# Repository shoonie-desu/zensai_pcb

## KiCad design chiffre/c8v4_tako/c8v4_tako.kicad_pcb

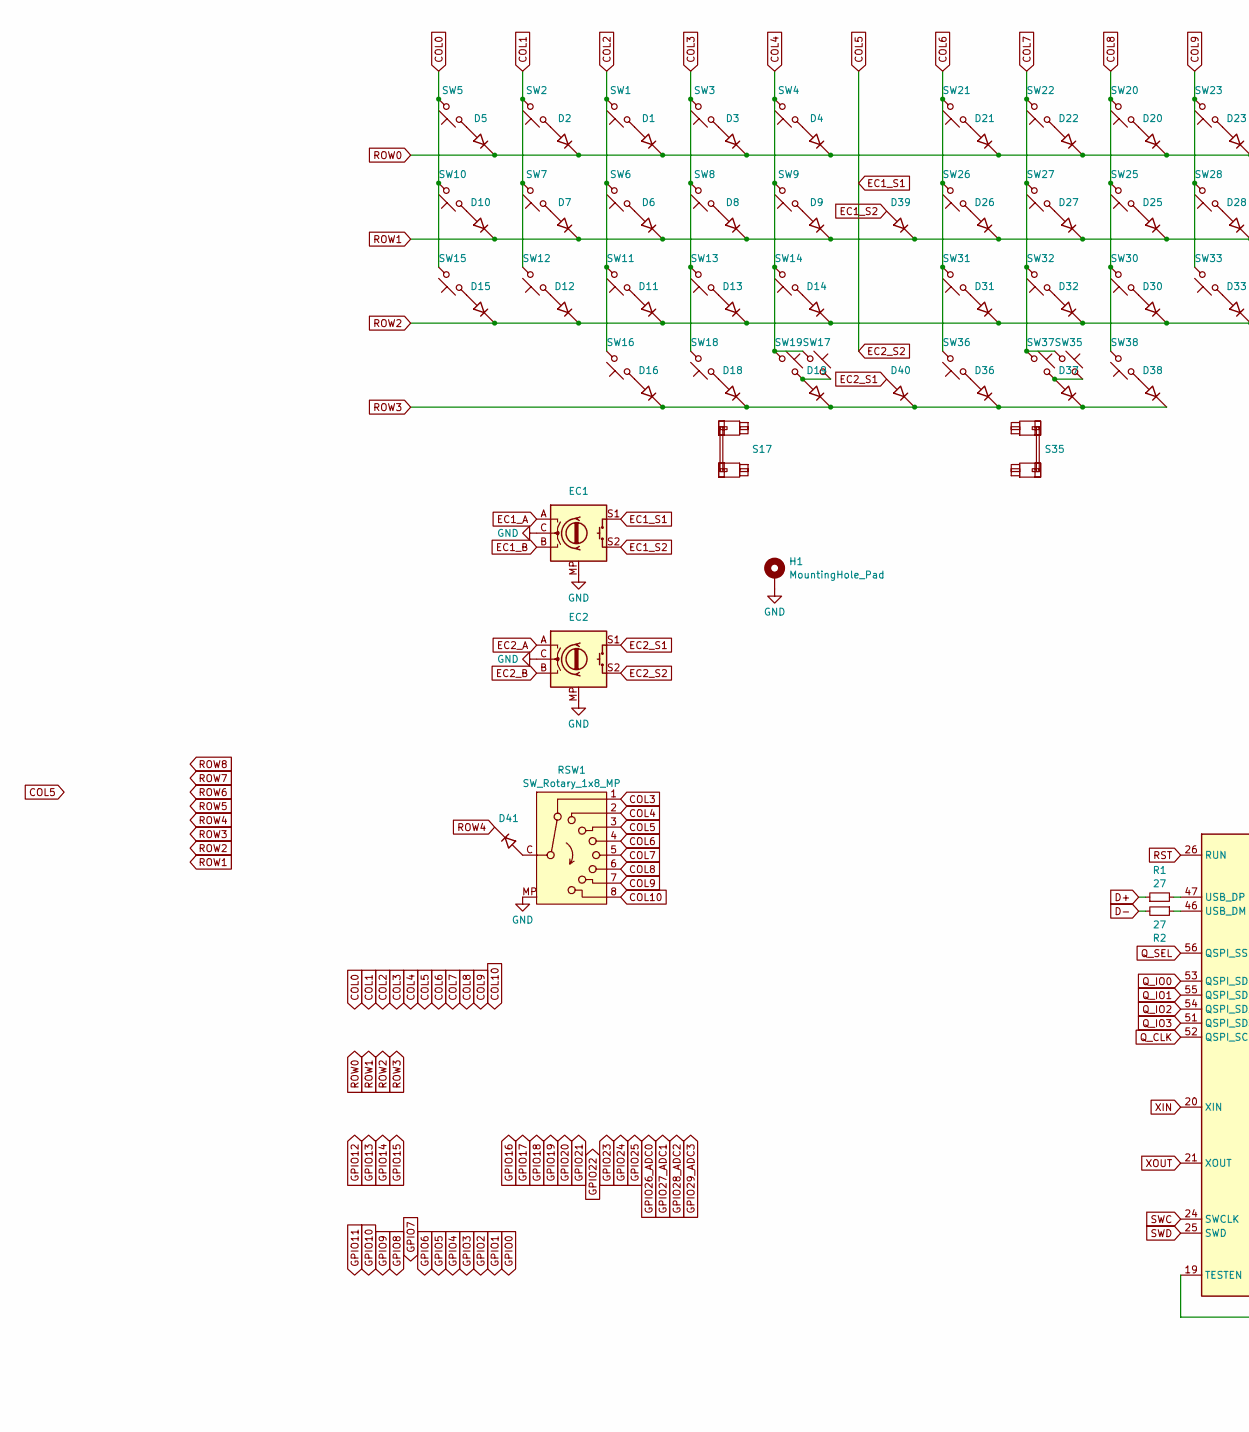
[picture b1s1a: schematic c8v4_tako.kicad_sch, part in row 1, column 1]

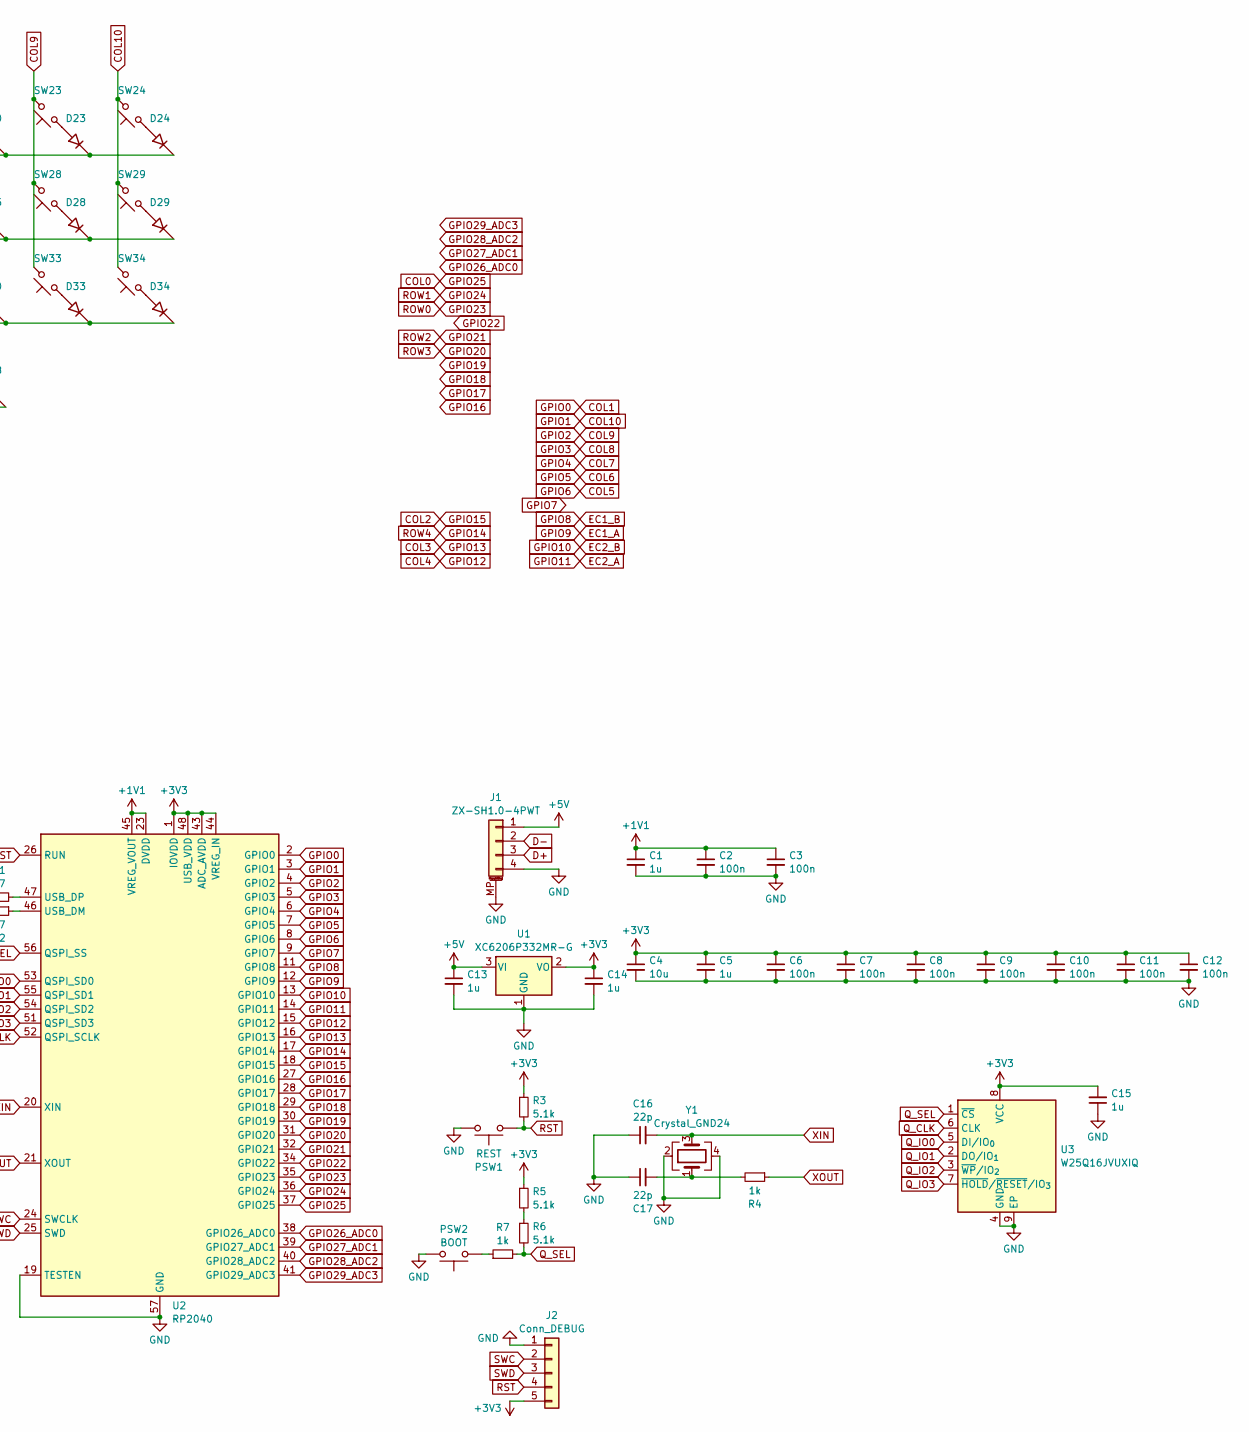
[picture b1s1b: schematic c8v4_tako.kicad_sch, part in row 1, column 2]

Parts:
C1, C5, C13, C14, C15: 1u; C_0402_1005Metric_mod
C2, C3, C6, C7, C8, C9, C10, C11, C12: 100n; C_0402_1005Metric_mod
C4: 10u; C_0402_1005Metric_mod
C16, C17: 22p; C_0402_1005Metric_mod
D1, D2, D3, D4, D5, D6, D7, D8, D9, D10, D11, D12, D13, D14, D15, D16, D18, D19, D20, D21, D22, D23, D24, D25, D26, D27, D28, D29, D30, D31, D32, D33, D34, D36, D37, D38, D39, D40, D41: 1N4148W; D_SOD-123_mod
EC1, EC2: RotaryEncoder_Switch_MP; ROT_Alps_EC11E-Switch_mod
H1: MountingHole_Pad; MountingHole_3.2mm_M3_Pad_TopBottom
J1: ZX-SH1.0-4PWT; JST_SH_SM04B-SRSS-TB_1x04-1MP_P1.00mm_Horizontal
J2: Conn_DEBUG; PinHeader_1x05_P1.27mm_Vertical
PSW1: REST; JUMP_REST_10.16mm
PSW2: BOOT; JUMP_BOOT_10.16mm
R1, R2: 27; R_0402_1005Metric
R3, R5, R6: 5.1k; R_0402_1005Metric
R4, R7: 1k; R_0402_1005Metric
RSW1: SW_Rotary_1x8_MP; alpsalpine_SRBV
S17, S35: MX_S; STAB_MX_2u
SW1, SW2, SW3, SW4, SW5, SW6, SW7, SW8, SW9, SW10, SW11, SW12, SW13, SW14, SW15, SW16, SW17, SW18, SW19, SW20, SW21, SW22, SW23, SW24, SW25, SW26, SW27, SW28, SW29, SW30, SW31, SW32, SW33, SW34, SW35, SW36, SW37, SW38: CPG151101S11; SW_MX_HS_S_CPG151101S11_1u_mod; LCSC Part # C49352235
U1: XC6206P332MR-G; SOT-23-3
U2: RP2040; QFN-56-1EP_7x7mm_P0.4mm_EP3.2x3.2mm; LCSC Part # C2040
U3: W25Q16JVUXIQ; Winbond_USON-8-1EP_3x2mm_P0.5mm_EP0.2x1.6mm
Y1: Crystal_GND24; Crystal_SMD_3225-4Pin_3.2x2.5mm; LCSC Part # C403945

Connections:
+1V1: C1.1, C2.1, C3.1, U2.23 (DVDD), U2.45 (VREG_VOUT), U2.50 (DVDD)
+3V3: C4.1, C5.1, C6.1, C7.1, C8.1, C9.1, C10.1, C11.1, C12.1, C14.1, C15.2, J2.5, R3.1, R5.1, U1.2 (VO), U2.1 (IOVDD), U2.10 (IOVDD), U2.22 (IOVDD), U2.33 (IOVDD), U2.42 (IOVDD), U2.43 (ADC_AVDD), U2.44 (VREG_IN), U2.48 (USB_VDD), U2.49 (IOVDD), U3.8 (VCC)
+5V: C13.1, J1.1, U1.3 (VI)
COL0: SW5.2, SW10.2, SW15.2, U2.37 (GPIO25)
COL1: SW2.2, SW7.2, SW12.2, U2.2 (GPIO0)
COL2: SW1.2, SW6.2, SW11.2, SW16.2, U2.18 (GPIO15)
COL3: RSW1.1, SW3.2, SW8.2, SW13.2, SW18.2, U2.16 (GPIO13)
COL4: RSW1.2, SW4.2, SW9.2, SW14.2, SW17.1, SW19.1, U2.15 (GPIO12)
COL5: EC1.S1, EC2.S2, RSW1.3, U2.8 (GPIO6)
COL6: RSW1.4, SW21.2, SW26.2, SW31.2, SW36.2, U2.7 (GPIO5)
COL7: RSW1.5, SW22.2, SW27.2, SW32.2, SW35.1, SW37.1, U2.6 (GPIO4)
COL8: RSW1.6, SW20.2, SW25.2, SW30.2, SW38.2, U2.5 (GPIO3)
COL9: RSW1.7, SW23.2, SW28.2, SW33.2, U2.4 (GPIO2)
COL10: RSW1.8, SW24.2, SW29.2, SW34.2, U2.3 (GPIO1)
D+: J1.3, R1.1
D-: J1.2, R2.2
EC1_A: EC1.A, U2.12 (GPIO9)
EC1_B: EC1.B, U2.11 (GPIO8)
EC1_S2: D39.2 (A), EC1.S2
EC2_A: EC2.A, U2.14 (GPIO11)
EC2_B: EC2.B, U2.13 (GPIO10)
EC2_S1: D40.2 (A), EC2.S1
GND: C1.2, C2.2, C3.2, C4.2, C5.2, C6.2, C7.2, C8.2, C9.2, C10.2, C11.2, C12.2, C13.2, C14.2, C15.1, C16.1, C17.1, EC1.C, EC1.MP, EC2.C, EC2.MP, H1.1, J1.4, J1.MP (MountPin), J2.1, PSW1.1, PSW2.1, RSW1.MP, U1.1 (GND), U2.19 (TESTEN), U2.57 (GND), U3.4 (GND), U3.9 (EP), Y1.2, Y1.4; also elsewhere on the board
GPIO7: U2.9 (GPIO7)
GPIO14: D41.1 (K), U2.17 (GPIO14)
GPIO16: U2.27 (GPIO16)
GPIO17: U2.28 (GPIO17)
GPIO18: U2.29 (GPIO18)
GPIO19: U2.30 (GPIO19)
GPIO20: D16.1 (K), D18.1 (K), D19.1 (K), D36.1 (K), D37.1 (K), D38.1 (K), D40.1 (K), U2.31 (GPIO20)
GPIO21: D11.1 (K), D12.1 (K), D13.1 (K), D14.1 (K), D15.1 (K), D30.1 (K), D31.1 (K), D32.1 (K), D33.1 (K), D34.1 (K), U2.32 (GPIO21)
GPIO22: U2.34 (GPIO22)
GPIO23: D1.1 (K), D2.1 (K), D3.1 (K), D4.1 (K), D5.1 (K), D20.1 (K), D21.1 (K), D22.1 (K), D23.1 (K), D24.1 (K), U2.35 (GPIO23)
GPIO24: D6.1 (K), D7.1 (K), D8.1 (K), D9.1 (K), D10.1 (K), D25.1 (K), D26.1 (K), D27.1 (K), D28.1 (K), D29.1 (K), D39.1 (K), U2.36 (GPIO24)
GPIO26_ADC0: U2.38 (GPIO26_ADC0)
GPIO27_ADC1: U2.39 (GPIO27_ADC1)
GPIO28_ADC2: U2.40 (GPIO28_ADC2)
GPIO29_ADC3: U2.41 (GPIO29_ADC3)
unnamed: C17.2, R4.2, Y1.1
unnamed: D1.2 (A), SW1.1
unnamed: D2.2 (A), SW2.1
unnamed: D3.2 (A), SW3.1
unnamed: D4.2 (A), SW4.1
unnamed: D5.2 (A), SW5.1
unnamed: D6.2 (A), SW6.1
unnamed: D7.2 (A), SW7.1
unnamed: D8.2 (A), SW8.1
unnamed: D9.2 (A), SW9.1
unnamed: D10.2 (A), SW10.1
unnamed: D11.2 (A), SW11.1
unnamed: D12.2 (A), SW12.1
unnamed: D13.2 (A), SW13.1
unnamed: D14.2 (A), SW14.1
unnamed: D15.2 (A), SW15.1
unnamed: D16.2 (A), SW16.1
unnamed: D18.2 (A), SW18.1
unnamed: D19.2 (A), SW17.2, SW19.2
unnamed: D20.2 (A), SW20.1
unnamed: D21.2 (A), SW21.1
unnamed: D22.2 (A), SW22.1
unnamed: D23.2 (A), SW23.1
unnamed: D24.2 (A), SW24.1
unnamed: D25.2 (A), SW25.1
unnamed: D26.2 (A), SW26.1
unnamed: D27.2 (A), SW27.1
unnamed: D28.2 (A), SW28.1
unnamed: D29.2 (A), SW29.1
unnamed: D30.2 (A), SW30.1
unnamed: D31.2 (A), SW31.1
unnamed: D32.2 (A), SW32.1
unnamed: D33.2 (A), SW33.1
unnamed: D34.2 (A), SW34.1
unnamed: D36.2 (A), SW36.1
unnamed: D37.2 (A), SW35.2, SW37.2
unnamed: D38.2 (A), SW38.1
unnamed: D41.2 (A), RSW1.C
unnamed: PSW2.2, R7.1
unnamed: R5.2, R6.1
unnamed: R2.1, U2.46 (USB_DM)
unnamed: R1.2, U2.47 (USB_DP)
Q_CLK: U2.52 (QSPI_SCLK), U3.6 (CLK)
Q_IO0: U2.53 (QSPI_SD0), U3.5 (DI/IO_{0})
Q_IO1: U2.55 (QSPI_SD1), U3.2 (DO/IO_{1})
Q_IO2: U2.54 (QSPI_SD2), U3.3 (~WP/IO_{2})
Q_IO3: U2.51 (QSPI_SD3), U3.7 (~HOLD/~RESET/IO_{3})
Q_SEL: R6.2, R7.2, U2.56 (QSPI_SS), U3.1 (~CS)
RST: J2.4, PSW1.2, R3.2, U2.26 (RUN)
SWC: J2.2, U2.24 (SWCLK)
SWD: J2.3, U2.25 (SWD)
XIN: C16.2, U2.20 (XIN), Y1.3
XOUT: R4.1, U2.21 (XOUT)

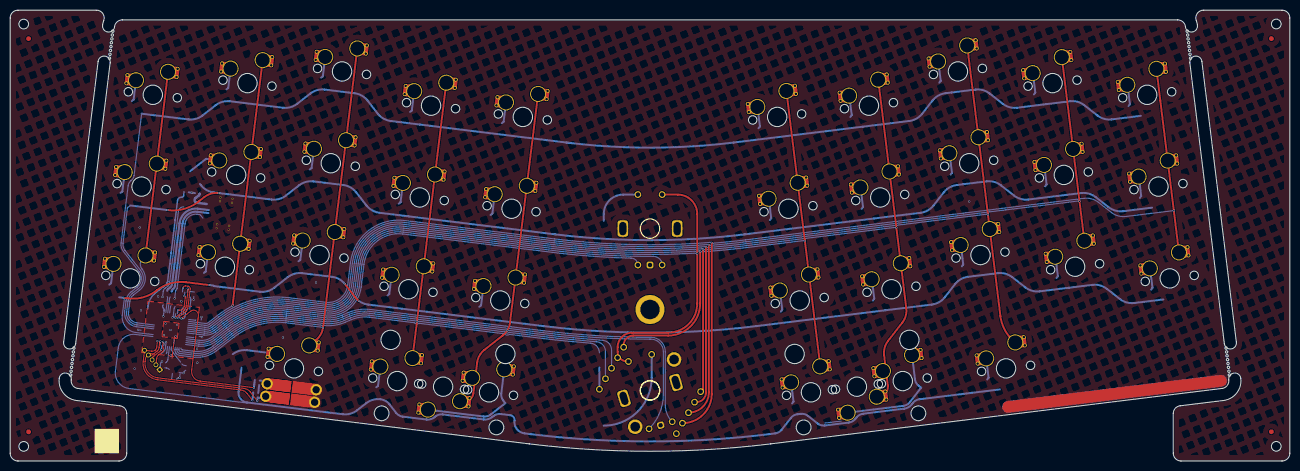
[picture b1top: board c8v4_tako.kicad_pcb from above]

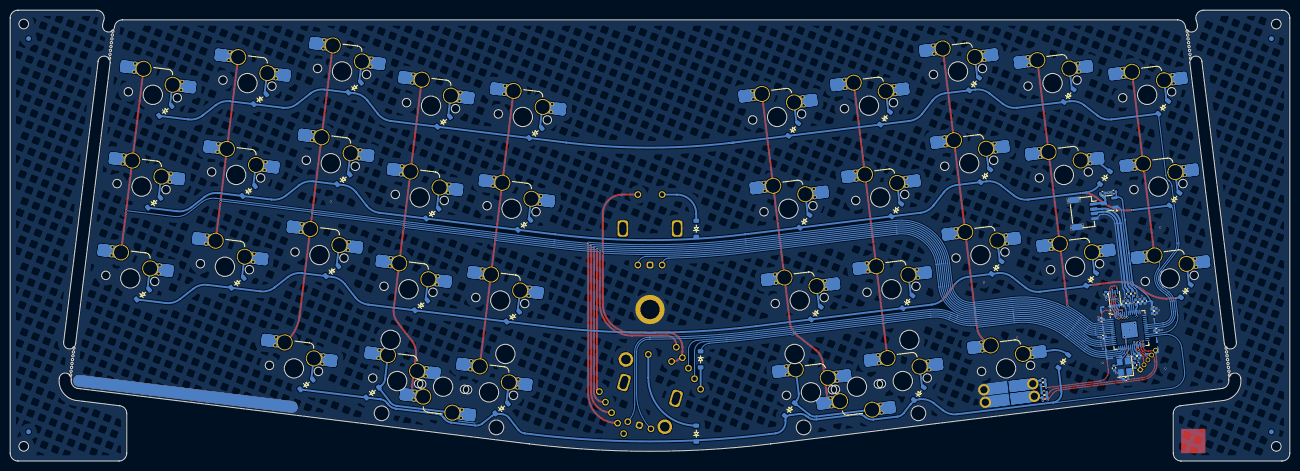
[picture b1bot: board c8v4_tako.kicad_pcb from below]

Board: 2 copper layers, 263.6 x 92.8 mm, 119 parts (112 on the bottom side), 81 nets.

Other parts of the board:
H1#2, H1#3, H1#4, H1#5: MountingHole_Pad; MountingHole_3.2mm_M3_Pad_TopBottom

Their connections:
GND: H1#2.1; also elsewhere on the board

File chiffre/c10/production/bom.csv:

Designator,Footprint,Quantity,Value,LCSC Part #
"C1, C13, C14, C15, C5",0402,5,1u,
"C10, C11, C12, C2, C3, C6, C7, C8, C9",0402,9,100n,
"C16, C17",0402,2,22p,
C4,0402,1,10u,
"D1, D10, D11, D12, D13, D14, D15, D16, D18, D19, D2, D20, D21, D22, D23, D24, D25, D26, D27, D28, D29, D3, D30, D31, D32, D33, D34, D36, D37, D38, D39, D4, D40, D41, D5, D6, D7, D8, D9",D_SOD-123_mod,39,1N4148W,
J1,JST_SH_SM04B-SRSS-TB_1x04-1MP_P1.00mm_Horizontal,1,ZX-SH1.0-4PWT,
"R1, R2",0402,2,27,
"R3, R5, R6",0402,3,5.1k,
"R4, R7",0402,2,1k,
RSW1,alpsalpine_SRBV,1,SW_Rotary_1x8_MP,
"SW1, SW10, SW11, SW12, SW13, SW14, SW15, SW16, SW17, SW18, SW19, SW2, SW20, SW21, SW22, SW23, SW24, SW25, SW26, SW27, SW28, SW29, SW3, SW30, SW31, SW32, SW33, SW34, SW35, SW36, SW37, SW38, SW4, SW5, SW6, SW7, SW8, SW9",SW_MX_HS_S_CPG151101S11_1u_mod,38,CPG151101S11,
U1,SOT-23-3,1,XC6206P332MR-G,
U2,QFN-56-1EP_7x7mm_P0.4mm_EP3.2x3.2mm,1,RP2040,
U3,Winbond_USON-8-1EP_3x2mm_P0.5mm_EP0.2x1.6mm,1,W25Q16JVUXIQ,
Y1,Crystal_SMD_3225-4Pin_3.2x2.5mm,1,Crystal_GND24,

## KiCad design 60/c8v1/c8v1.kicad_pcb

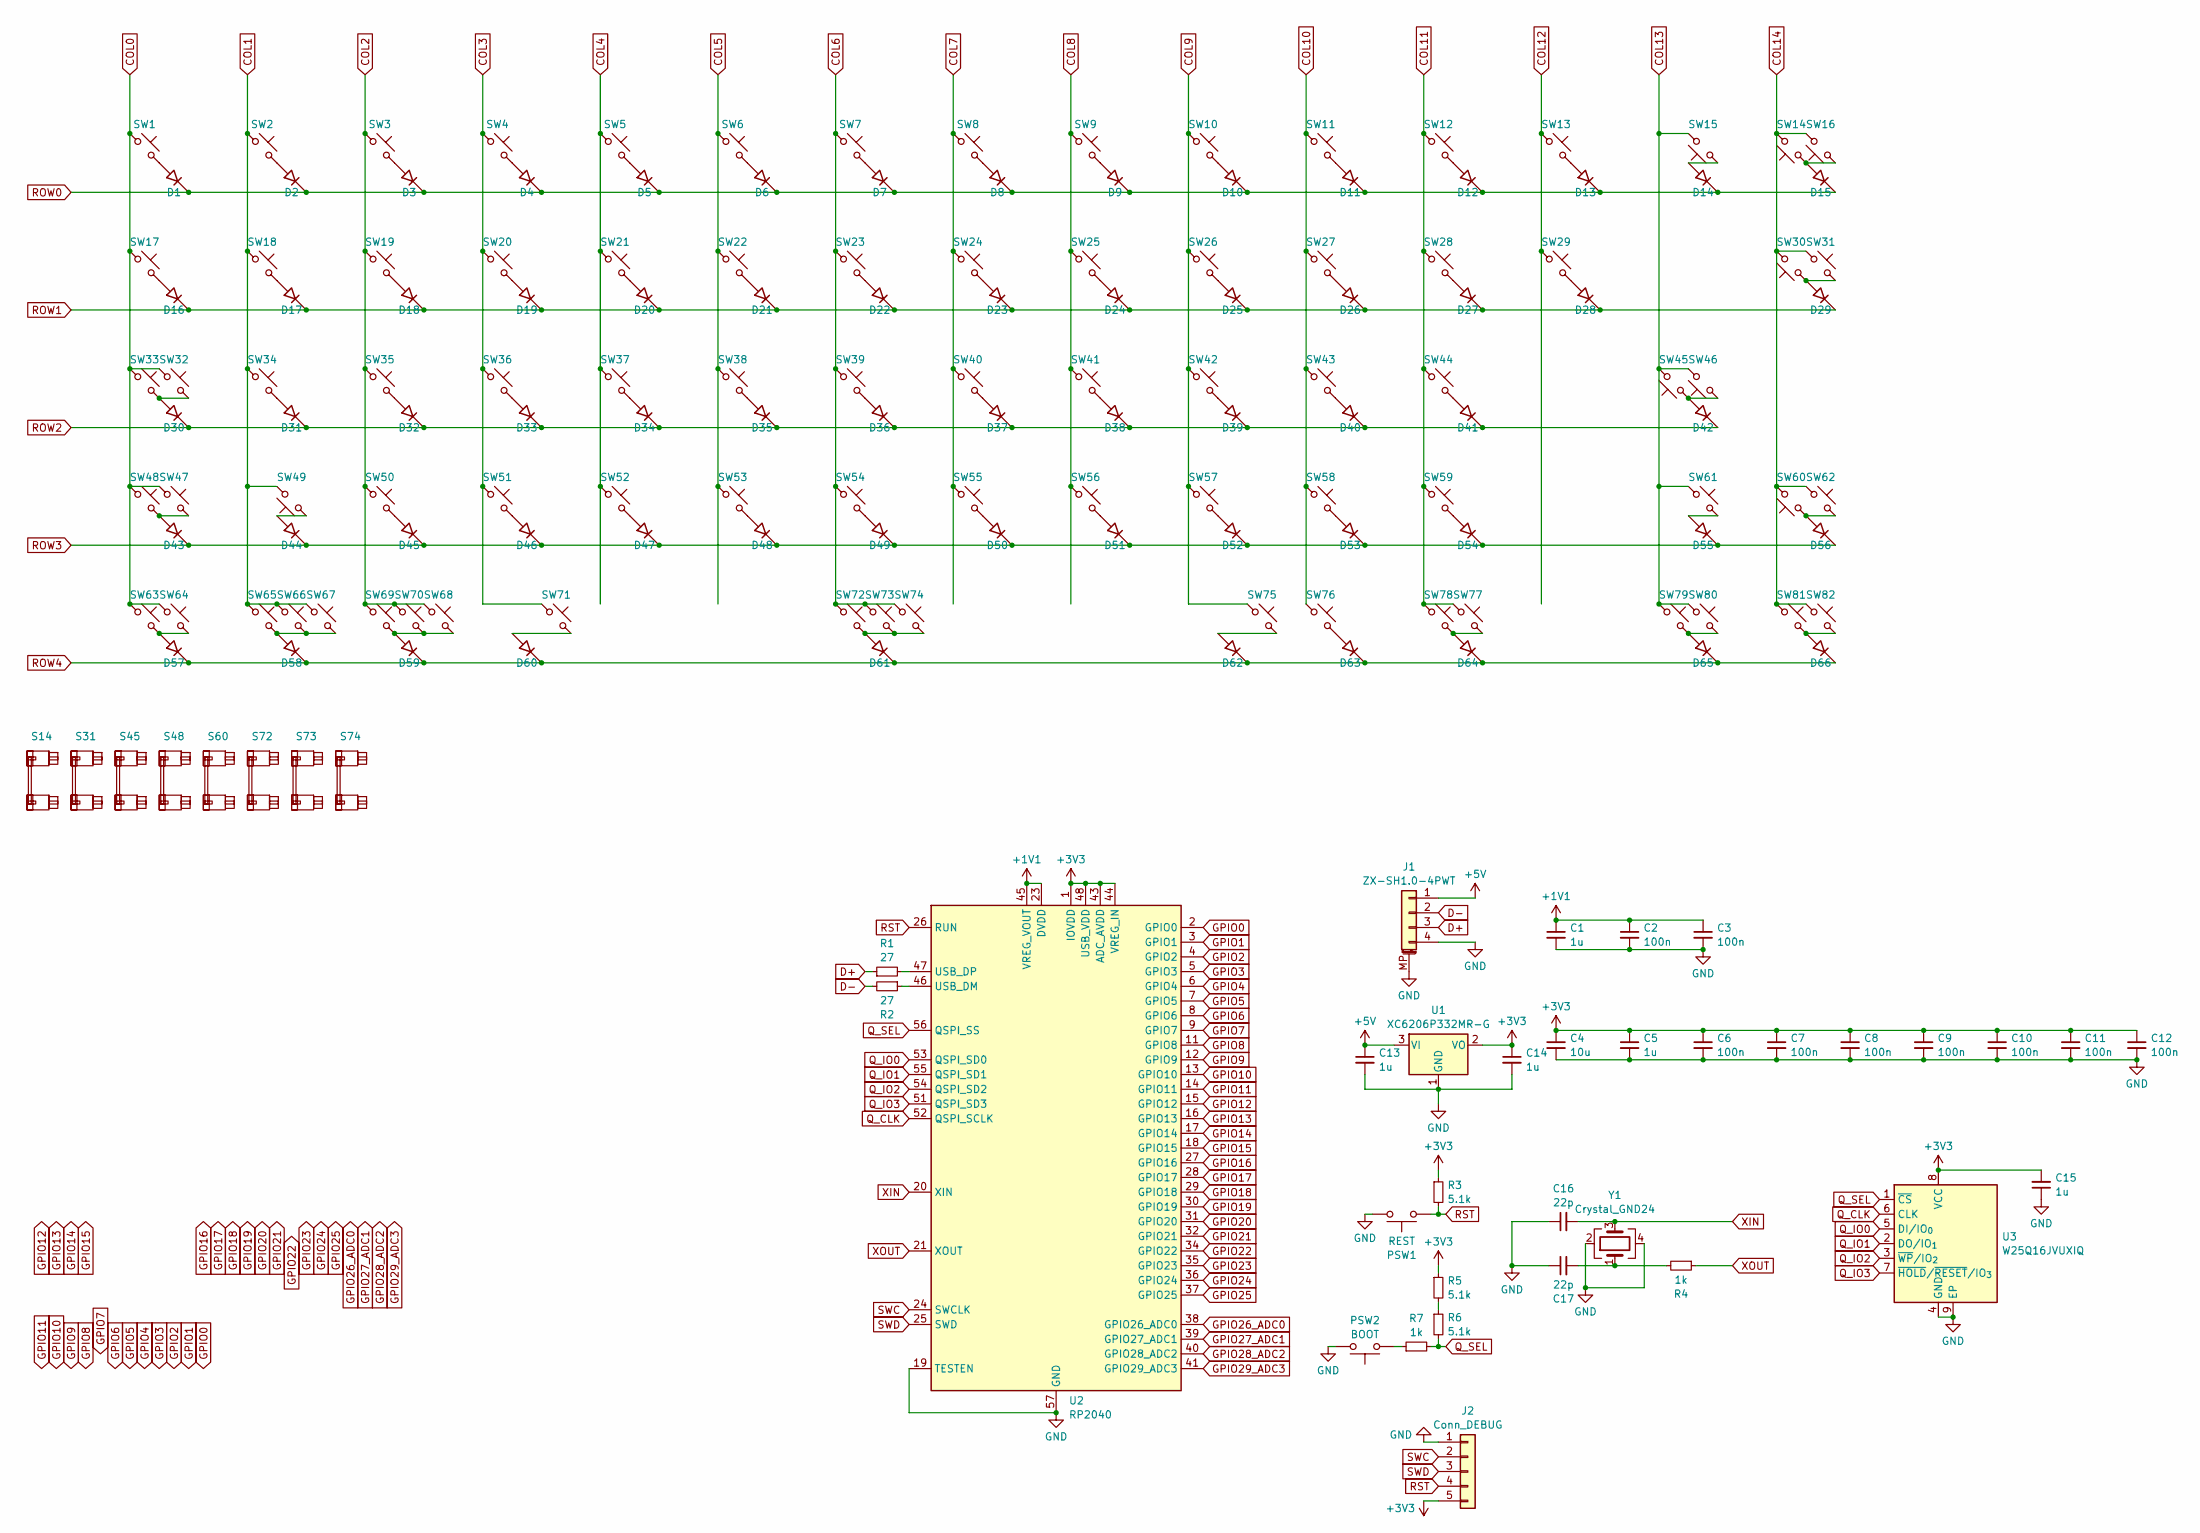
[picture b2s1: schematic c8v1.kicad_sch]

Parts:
C1, C5, C13, C14, C15: 1u; C_0402_1005Metric_mod
C2, C3, C6, C7, C8, C9, C10, C11, C12: 100n; C_0402_1005Metric_mod
C4: 10u; C_0402_1005Metric_mod
C16, C17: 22p; C_0402_1005Metric_mod
D1, D2, D3, D4, D5, D6, D7, D8, D9, D10, D11, D12, D13, D14, D15, D16, D17, D18, D19, D20, D21, D22, D23, D24, D25, D26, D27, D28, D29, D30, D31, D32, D33, D34, D35, D36, D37, D38, D39, D40, D41, D42, D43, D44, D45, D46, D47, D48, D49, D50, D51, D52, D53, D54, D55, D56, D57, D58, D59, D60, D61, D62, D63, D64, D65, D66: 1N4148W; D_SOD-123_mod
J1: ZX-SH1.0-4PWT; JST_SH_SM04B-SRSS-TB_1x04-1MP_P1.00mm_Horizontal
J2: Conn_DEBUG; PinHeader_1x05_P1.27mm_Vertical
PSW1: REST; JUMP_REST_10.16mm
PSW2: BOOT; JUMP_BOOT_10.16mm
R1, R2: 27; R_0402_1005Metric
R3, R5, R6: 5.1k; R_0402_1005Metric
R4, R7: 1k; R_0402_1005Metric
S14, S31, S45, S48, S60: MX_S; STAB_MX_2u
S72: MX_S; STAB_MX_4.5u
S73: MX_S; STAB_MX_6.25u
S74: MX_S; STAB_MX_7u
SW1, SW2, SW3, SW4, SW5, SW6, SW7, SW8, SW9, SW10, SW11, SW12, SW13, SW14, SW15, SW16, SW17, SW18, SW19, SW20, SW21, SW22, SW23, SW24, SW25, SW26, SW27, SW28, SW29, SW30, SW31, SW32, SW33, SW34, SW35, SW36, SW37, SW38, SW39, SW40, SW41, SW42, SW43, SW44, SW45, SW46, SW47, SW48, SW49, SW50, SW51, SW52, SW53, SW54, SW55, SW56, SW57, SW58, SW59, SW60, SW61, SW62, SW63, SW64, SW65, SW66, SW67, SW68, SW69, SW70, SW71, SW72, SW73, SW74, SW75, SW76, SW77, SW78, SW79, SW80, SW81, SW82: CPG151101S11; SW_MX_1u_mod
U1: XC6206P332MR-G; SOT-23-3
U2: RP2040; QFN-56-1EP_7x7mm_P0.4mm_EP3.2x3.2mm
U3: W25Q16JVUXIQ; Winbond_USON-8-1EP_3x2mm_P0.5mm_EP0.2x1.6mm
Y1: Crystal_GND24; Crystal_SMD_3225-4Pin_3.2x2.5mm

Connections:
+1V1: C1.1, C2.1, C3.1, U2.23 (DVDD), U2.45 (VREG_VOUT), U2.50 (DVDD)
+3V3: C4.1, C5.1, C6.1, C7.1, C8.1, C9.1, C10.1, C11.1, C12.1, C14.1, C15.2, J2.5, R3.1, R5.1, U1.2 (VO), U2.1 (IOVDD), U2.10 (IOVDD), U2.22 (IOVDD), U2.33 (IOVDD), U2.42 (IOVDD), U2.43 (ADC_AVDD), U2.44 (VREG_IN), U2.48 (USB_VDD), U2.49 (IOVDD), U3.8 (VCC)
+5V: C13.1, J1.1, U1.3 (VI)
COL0: SW1.1, SW17.1, SW32.1, SW33.1, SW47.1, SW48.1, SW63.1, SW64.1
COL1: SW2.1, SW18.1, SW34.1, SW49.2, SW65.1, SW66.1, SW67.1
COL2: SW3.1, SW19.1, SW35.1, SW50.1, SW68.1, SW69.1, SW70.1
COL3: SW4.1, SW20.1, SW36.1, SW51.1, SW71.1
COL4: SW5.1, SW21.1, SW37.1, SW52.1
COL5: SW6.1, SW22.1, SW38.1, SW53.1
COL6: SW7.1, SW23.1, SW39.1, SW54.1, SW72.1, SW73.1, SW74.1
COL7: SW8.1, SW24.1, SW40.1, SW55.1
COL8: SW9.1, SW25.1, SW41.1, SW56.1
COL9: SW10.1, SW26.1, SW42.1, SW57.1, SW75.1
COL10: SW11.1, SW27.1, SW43.1, SW58.1, SW76.1
COL11: SW12.1, SW28.1, SW44.1, SW59.1, SW77.1, SW78.1
COL12: SW13.1, SW29.1
COL13: SW15.2, SW45.2, SW46.2, SW61.1, SW79.1, SW80.1
COL14: SW14.2, SW16.2, SW30.2, SW31.1, SW60.2, SW62.1, SW81.1, SW82.1
D+: J1.3, R1.1
D-: J1.2, R2.2
GND: C1.2, C2.2, C3.2, C4.2, C5.2, C6.2, C7.2, C8.2, C9.2, C10.2, C11.2, C12.2, C13.2, C14.2, C15.1, C16.1, C17.1, J1.4, J1.MP (MountPin), J2.1, PSW1.1, PSW2.1, U1.1 (GND), U2.19 (TESTEN), U2.57 (GND), U3.4 (GND), U3.9 (EP), Y1.2, Y1.4
GPIO0: U2.2 (GPIO0)
GPIO1: U2.3 (GPIO1)
GPIO2: U2.4 (GPIO2)
GPIO3: U2.5 (GPIO3)
GPIO4: U2.6 (GPIO4)
GPIO5: U2.7 (GPIO5)
GPIO6: U2.8 (GPIO6)
GPIO7: U2.9 (GPIO7)
GPIO8: U2.11 (GPIO8)
GPIO9: U2.12 (GPIO9)
GPIO10: U2.13 (GPIO10)
GPIO11: U2.14 (GPIO11)
GPIO12: U2.15 (GPIO12)
GPIO13: U2.16 (GPIO13)
GPIO14: U2.17 (GPIO14)
GPIO15: U2.18 (GPIO15)
GPIO16: U2.27 (GPIO16)
GPIO17: U2.28 (GPIO17)
GPIO18: U2.29 (GPIO18)
GPIO19: U2.30 (GPIO19)
GPIO20: U2.31 (GPIO20)
GPIO21: U2.32 (GPIO21)
GPIO22: U2.34 (GPIO22)
GPIO23: U2.35 (GPIO23)
GPIO24: U2.36 (GPIO24)
GPIO25: U2.37 (GPIO25)
GPIO26_ADC0: U2.38 (GPIO26_ADC0)
GPIO27_ADC1: U2.39 (GPIO27_ADC1)
GPIO28_ADC2: U2.40 (GPIO28_ADC2)
GPIO29_ADC3: U2.41 (GPIO29_ADC3)
unnamed: C17.2, R4.2, Y1.1
unnamed: D1.2 (A), SW1.2
unnamed: D2.2 (A), SW2.2
unnamed: D3.2 (A), SW3.2
unnamed: D4.2 (A), SW4.2
unnamed: D5.2 (A), SW5.2
unnamed: D6.2 (A), SW6.2
unnamed: D7.2 (A), SW7.2
unnamed: D8.2 (A), SW8.2
unnamed: D9.2 (A), SW9.2
unnamed: D10.2 (A), SW10.2
unnamed: D11.2 (A), SW11.2
unnamed: D12.2 (A), SW12.2
unnamed: D13.2 (A), SW13.2
unnamed: D14.2 (A), SW15.1
unnamed: D15.2 (A), SW14.1, SW16.1
unnamed: D16.2 (A), SW17.2
unnamed: D17.2 (A), SW18.2
unnamed: D18.2 (A), SW19.2
unnamed: D19.2 (A), SW20.2
unnamed: D20.2 (A), SW21.2
unnamed: D21.2 (A), SW22.2
unnamed: D22.2 (A), SW23.2
unnamed: D23.2 (A), SW24.2
unnamed: D24.2 (A), SW25.2
unnamed: D25.2 (A), SW26.2
unnamed: D26.2 (A), SW27.2
unnamed: D27.2 (A), SW28.2
unnamed: D28.2 (A), SW29.2
unnamed: D29.2 (A), SW30.1, SW31.2
unnamed: D30.2 (A), SW32.2, SW33.2
unnamed: D31.2 (A), SW34.2
unnamed: D32.2 (A), SW35.2
unnamed: D33.2 (A), SW36.2
unnamed: D34.2 (A), SW37.2
unnamed: D35.2 (A), SW38.2
unnamed: D36.2 (A), SW39.2
unnamed: D37.2 (A), SW40.2
unnamed: D38.2 (A), SW41.2
unnamed: D39.2 (A), SW42.2
unnamed: D40.2 (A), SW43.2
unnamed: D41.2 (A), SW44.2
unnamed: D42.2 (A), SW45.1, SW46.1
unnamed: D43.2 (A), SW47.2, SW48.2
unnamed: D44.2 (A), SW49.1
unnamed: D45.2 (A), SW50.2
unnamed: D46.2 (A), SW51.2
unnamed: D47.2 (A), SW52.2
unnamed: D48.2 (A), SW53.2
unnamed: D49.2 (A), SW54.2
unnamed: D50.2 (A), SW55.2
unnamed: D51.2 (A), SW56.2
unnamed: D52.2 (A), SW57.2
unnamed: D53.2 (A), SW58.2
unnamed: D54.2 (A), SW59.2
unnamed: D55.2 (A), SW61.2
unnamed: D56.2 (A), SW60.1, SW62.2
unnamed: D57.2 (A), SW63.2, SW64.2
unnamed: D58.2 (A), SW65.2, SW66.2, SW67.2
unnamed: D59.2 (A), SW68.2, SW69.2, SW70.2
unnamed: D60.2 (A), SW71.2
unnamed: D61.2 (A), SW72.2, SW73.2, SW74.2
unnamed: D62.2 (A), SW75.2
unnamed: D63.2 (A), SW76.2
unnamed: D64.2 (A), SW77.2, SW78.2
unnamed: D65.2 (A), SW79.2, SW80.2
unnamed: D66.2 (A), SW81.2, SW82.2
unnamed: PSW2.2, R7.1
unnamed: R5.2, R6.1
unnamed: R2.1, U2.46 (USB_DM)
unnamed: R1.2, U2.47 (USB_DP)
Q_CLK: U2.52 (QSPI_SCLK), U3.6 (CLK)
Q_IO0: U2.53 (QSPI_SD0), U3.5 (DI/IO_{0})
Q_IO1: U2.55 (QSPI_SD1), U3.2 (DO/IO_{1})
Q_IO2: U2.54 (QSPI_SD2), U3.3 (~WP/IO_{2})
Q_IO3: U2.51 (QSPI_SD3), U3.7 (~HOLD/~RESET/IO_{3})
Q_SEL: R6.2, R7.2, U2.56 (QSPI_SS), U3.1 (~CS)
ROW0: D1.1 (K), D2.1 (K), D3.1 (K), D4.1 (K), D5.1 (K), D6.1 (K), D7.1 (K), D8.1 (K), D9.1 (K), D10.1 (K), D11.1 (K), D12.1 (K), D13.1 (K), D14.1 (K), D15.1 (K)
ROW1: D16.1 (K), D17.1 (K), D18.1 (K), D19.1 (K), D20.1 (K), D21.1 (K), D22.1 (K), D23.1 (K), D24.1 (K), D25.1 (K), D26.1 (K), D27.1 (K), D28.1 (K), D29.1 (K)
ROW2: D30.1 (K), D31.1 (K), D32.1 (K), D33.1 (K), D34.1 (K), D35.1 (K), D36.1 (K), D37.1 (K), D38.1 (K), D39.1 (K), D40.1 (K), D41.1 (K), D42.1 (K)
ROW3: D43.1 (K), D44.1 (K), D45.1 (K), D46.1 (K), D47.1 (K), D48.1 (K), D49.1 (K), D50.1 (K), D51.1 (K), D52.1 (K), D53.1 (K), D54.1 (K), D55.1 (K), D56.1 (K)
ROW4: D57.1 (K), D58.1 (K), D59.1 (K), D60.1 (K), D61.1 (K), D62.1 (K), D63.1 (K), D64.1 (K), D65.1 (K), D66.1 (K)
RST: J2.4, PSW1.2, R3.2, U2.26 (RUN)
SWC: J2.2, U2.24 (SWCLK)
SWD: J2.3, U2.25 (SWD)
XIN: C16.2, U2.20 (XIN), Y1.3
XOUT: R4.1, U2.21 (XOUT)

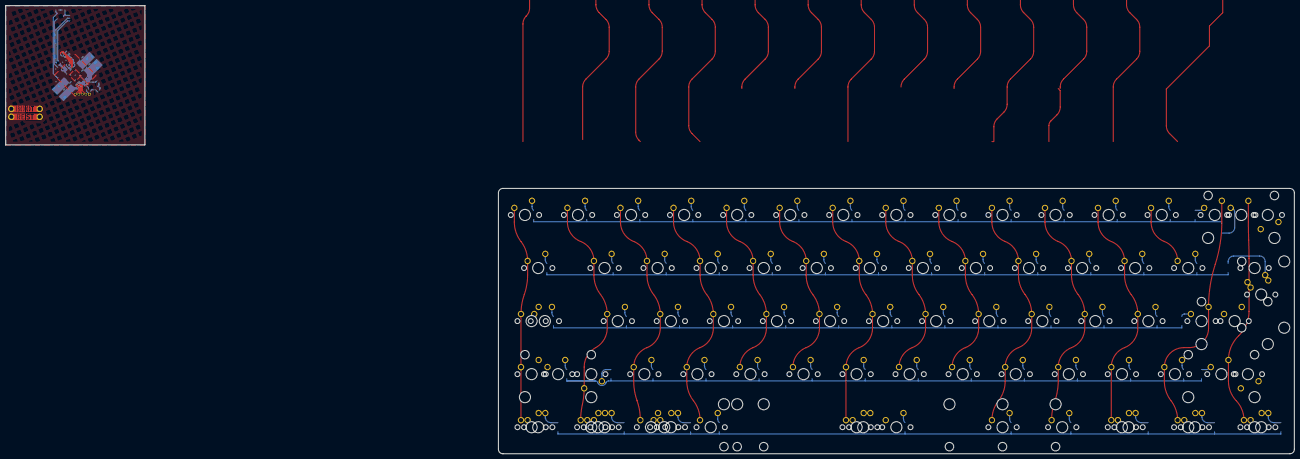
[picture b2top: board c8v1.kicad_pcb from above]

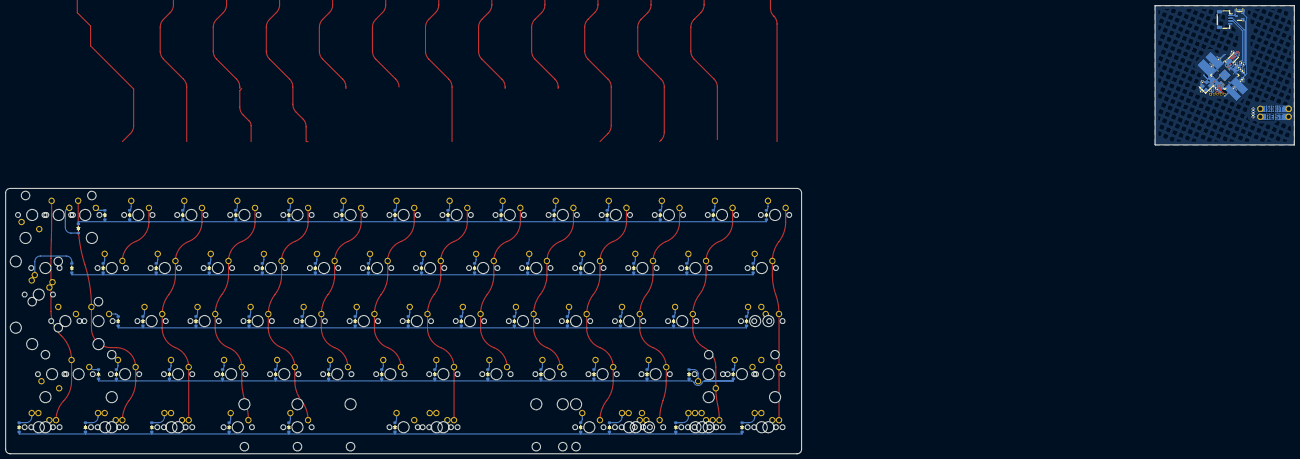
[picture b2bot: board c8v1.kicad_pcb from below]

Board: 2 copper layers, 285.8 x 95.2 mm, 188 parts (95 on the bottom side), 108 nets.

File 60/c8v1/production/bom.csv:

Designator,Footprint,Quantity,Value,LCSC Part #
"_2, ",,2,,
"C1, C13, C14, C15, C5",0402,5,1u,
"C10, C11, C12, C2, C3, C6, C7, C8, C9",0402,9,100n,
"C16, C17",0402,2,22p,
C4,0402,1,10u,
"D1, D10, D11, D12, D13, D14, D15, D16, D18, D19, D2, D20, D21, D22, D23, D24, D25, D26, D27, D28, D29, D3, D30, D31, D32, D33, D34, D36, D37, D38, D39, D4, D40, D41, D5, D6, D7, D8, D9",D_SOD-123_mod,39,1N4148W,
J1,JST_SH_SM04B-SRSS-TB_1x04-1MP_P1.00mm_Horizontal,1,ZX-SH1.0-4PWT,
"R1, R2",0402,2,27,
"R3, R5, R6",0402,3,5.1k,
"R4, R7",0402,2,1k,
RSW1,alpsalpine_SRBV,1,SW_Rotary_1x8_MP,
"SW1, SW10, SW11, SW12, SW13, SW14, SW15, SW16, SW17, SW18, SW19, SW2, SW20, SW21, SW22, SW23, SW24, SW25, SW26, SW27, SW28, SW29, SW3, SW30, SW31, SW32, SW33, SW34, SW35, SW36, SW37, SW38, SW4, SW5, SW6, SW7, SW8, SW9",SW_MX_HS_S_CPG151101S11_1u_mod,38,CPG151101S11,
U1,SOT-23-3,1,XC6206P332MR-G,
U2,QFN-56-1EP_7x7mm_P0.4mm_EP3.2x3.2mm,1,RP2040,
U3,Winbond_USON-8-1EP_3x2mm_P0.5mm_EP0.2x1.6mm,1,W25Q16JVUXIQ,
Y1,Crystal_SMD_3225-4Pin_3.2x2.5mm,1,Crystal_GND24,
